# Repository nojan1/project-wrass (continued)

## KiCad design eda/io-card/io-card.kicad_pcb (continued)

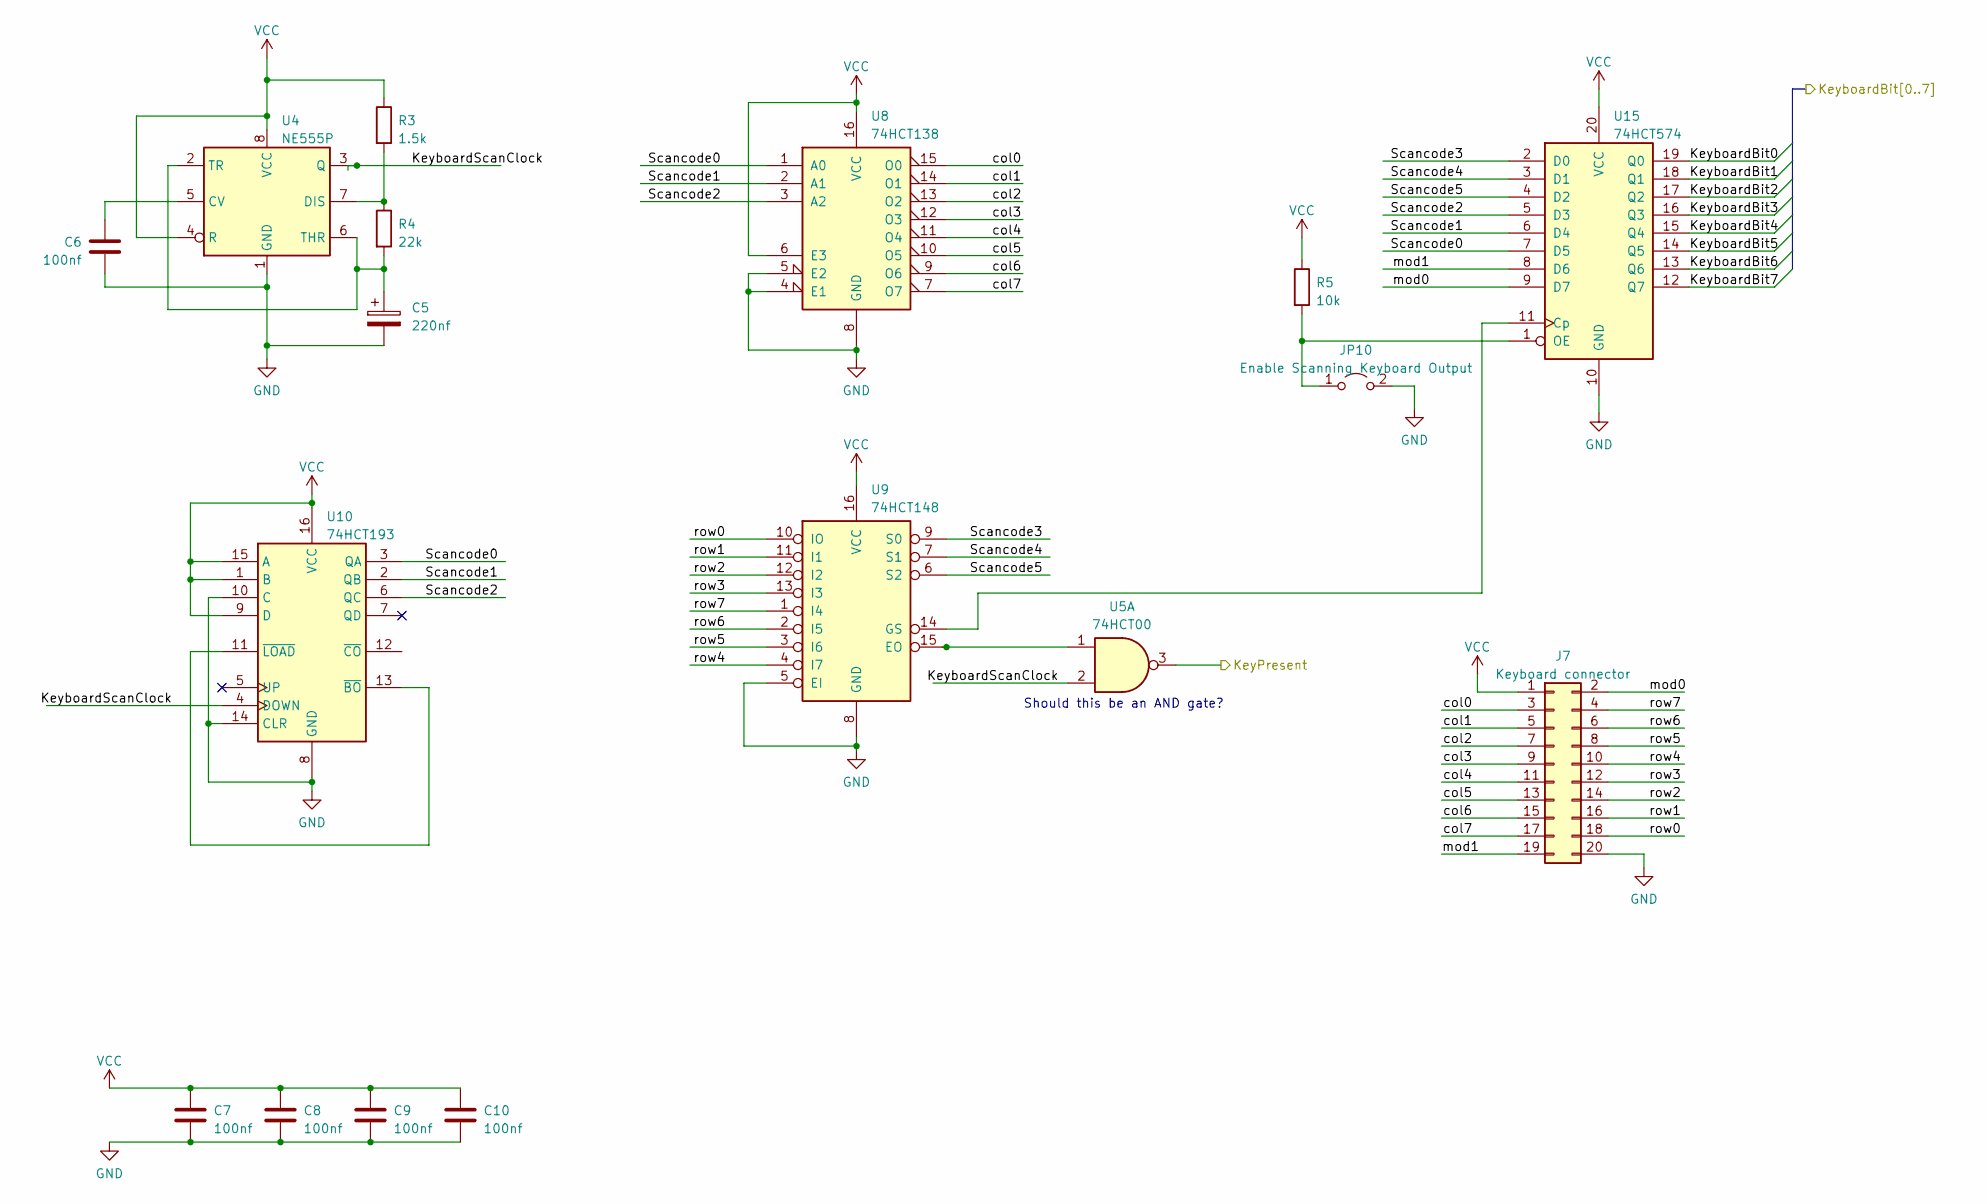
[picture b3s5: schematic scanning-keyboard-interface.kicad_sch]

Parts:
C5: 220nf; C_Radial_D4.0mm_H5.0mm_P1.50mm
C6, C7, C8, C9, C10: 100nf; C_Disc_D3.8mm_W2.6mm_P2.50mm
J7: Keyboard connector; PinHeader_2x10_P2.54mm_Horizontal
JP10: Enable Scanning Keyboard Output; PinHeader_1x02_P2.54mm_Vertical
R3: 1.5k; R_Axial_DIN0204_L3.6mm_D1.6mm_P5.08mm_Horizontal
R4: 22k; R_Axial_DIN0204_L3.6mm_D1.6mm_P5.08mm_Horizontal
R5: 10k; R_Axial_DIN0204_L3.6mm_D1.6mm_P5.08mm_Horizontal
U4: NE555P; DIP-8_W7.62mm
U5: 74HCT00; DIP-14_W7.62mm
U8: 74HCT138; DIP-16_W7.62mm
U9: 74HCT148; DIP-16_W7.62mm
U10: 74HCT193; DIP-16_W7.62mm
U15: 74HCT574; DIP-20_W7.62mm

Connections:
/PS2 keyboard interface/KeyboardBit0: U15.19 (Q0); also elsewhere on the board
/PS2 keyboard interface/KeyboardBit1: U15.18 (Q1); also elsewhere on the board
/PS2 keyboard interface/KeyboardBit2: U15.17 (Q2); also elsewhere on the board
/PS2 keyboard interface/KeyboardBit3: U15.16 (Q3); also elsewhere on the board
/PS2 keyboard interface/KeyboardBit4: U15.15 (Q4); also elsewhere on the board
/PS2 keyboard interface/KeyboardBit5: U15.14 (Q5); also elsewhere on the board
/PS2 keyboard interface/KeyboardBit6: U15.13 (Q6); also elsewhere on the board
/PS2 keyboard interface/KeyboardBit7: U15.12 (Q7); also elsewhere on the board
/Scanning keyboard interface/KeyPresent: U5.3; also elsewhere on the board
/Scanning keyboard interface/KeyboardScanClock: U4.3 (Q), U5.2, U10.4 (DOWN)
/Scanning keyboard interface/Scancode0: U8.1 (A0), U10.3 (QA), U15.7 (D5)
/Scanning keyboard interface/Scancode1: U8.2 (A1), U10.2 (QB), U15.6 (D4)
/Scanning keyboard interface/Scancode2: U8.3 (A2), U10.6 (QC), U15.5 (D3)
/Scanning keyboard interface/Scancode3: U9.9 (S0), U15.2 (D0)
/Scanning keyboard interface/Scancode4: U9.7 (S1), U15.3 (D1)
/Scanning keyboard interface/Scancode5: U9.6 (S2), U15.4 (D2)
/Scanning keyboard interface/col0: J7.3, U8.15 (O0)
/Scanning keyboard interface/col1: J7.5, U8.14 (O1)
/Scanning keyboard interface/col2: J7.7, U8.13 (O2)
/Scanning keyboard interface/col3: J7.9, U8.12 (O3)
/Scanning keyboard interface/col4: J7.11, U8.11 (O4)
/Scanning keyboard interface/col5: J7.13, U8.10 (O5)
/Scanning keyboard interface/col6: J7.15, U8.9 (O6)
/Scanning keyboard interface/col7: J7.17, U8.7 (O7)
/Scanning keyboard interface/mod0: J7.2, U15.9 (D7)
/Scanning keyboard interface/mod1: J7.19, U15.8 (D6)
/Scanning keyboard interface/row0: J7.18, U9.10 (IO)
/Scanning keyboard interface/row1: J7.16, U9.11 (I1)
/Scanning keyboard interface/row2: J7.14, U9.12 (I2)
/Scanning keyboard interface/row3: J7.12, U9.13 (I3)
/Scanning keyboard interface/row4: J7.10, U9.4 (I7)
/Scanning keyboard interface/row5: J7.8, U9.3 (I6)
/Scanning keyboard interface/row6: J7.6, U9.2 (I5)
/Scanning keyboard interface/row7: J7.4, U9.1 (I4)
GND: C5.2, C6.2, C7.2, C8.2, C9.2, C10.2, J7.20, JP10.2 (B), U4.1 (GND), U8.4 (E1), U8.5 (E2), U8.8 (GND), U9.5 (EI), U9.8 (GND), U10.8 (GND), U10.10 (C), U10.14 (CLR), U15.10 (GND); also elsewhere on the board
unnamed: JP10.1 (A), R5.2, U15.1 (OE)
unnamed: C6.1, U4.5 (CV)
unnamed: R3.2, R4.1, U4.7 (DIS)
unnamed: C5.1, R4.2, U4.2 (TR), U4.6 (THR)
unnamed: U5.1, U9.15 (EO)
unnamed: U10.11 (~LOAD), U10.13 (~BO)
unnamed: U9.14 (GS), U15.11 (Cp)
VCC: C7.1, C8.1, C9.1, C10.1, J7.1, R3.1, R5.1, U4.4 (R), U4.8 (VCC), U8.6 (E3), U8.16 (VCC), U9.16 (VCC), U10.1 (B), U10.9 (D), U10.15 (A), U10.16 (VCC), U15.20 (VCC); also elsewhere on the board

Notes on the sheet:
Should this be an AND gate?

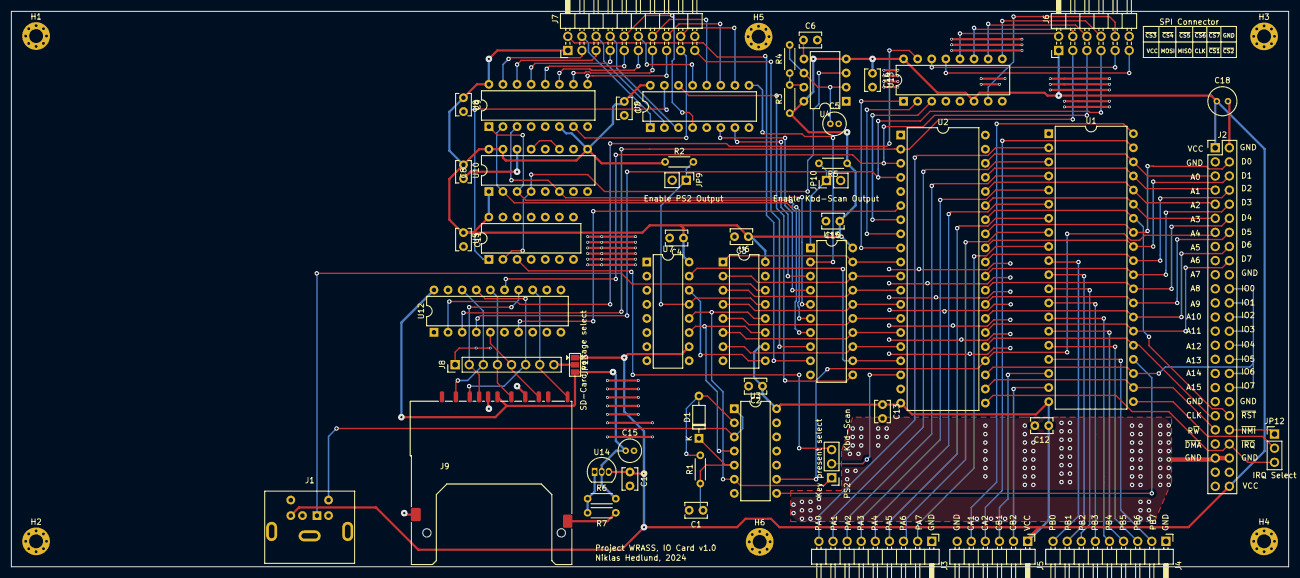
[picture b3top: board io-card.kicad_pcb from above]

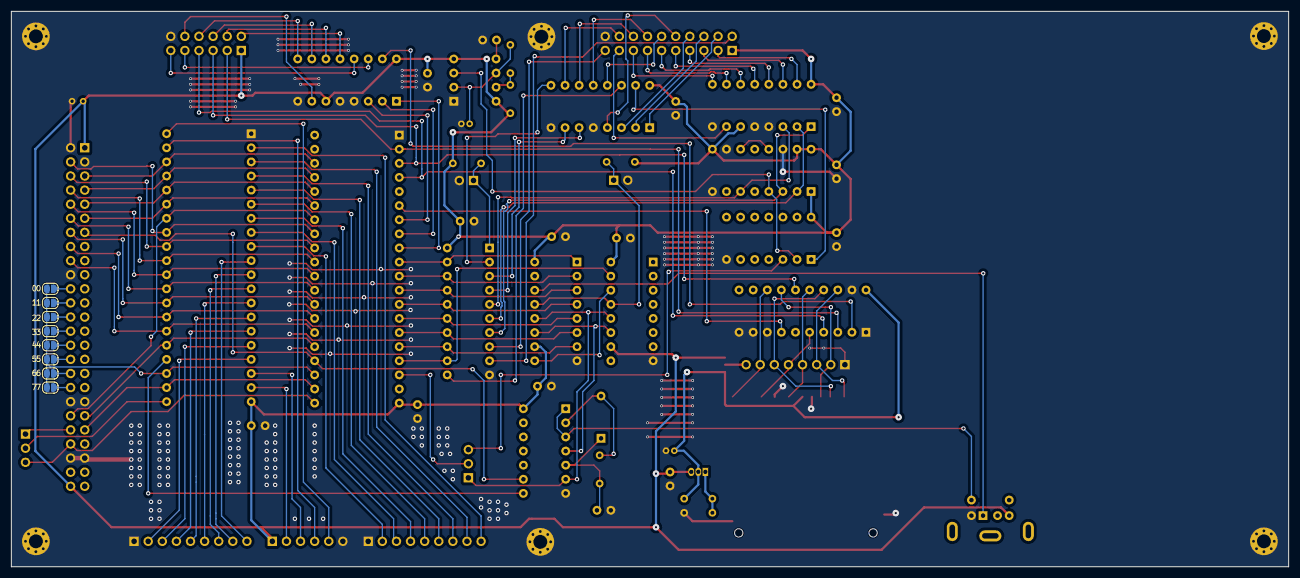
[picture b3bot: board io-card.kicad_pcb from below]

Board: 2 copper layers, 230.0 x 100.0 mm, 67 parts (8 on the bottom side), 125 nets.

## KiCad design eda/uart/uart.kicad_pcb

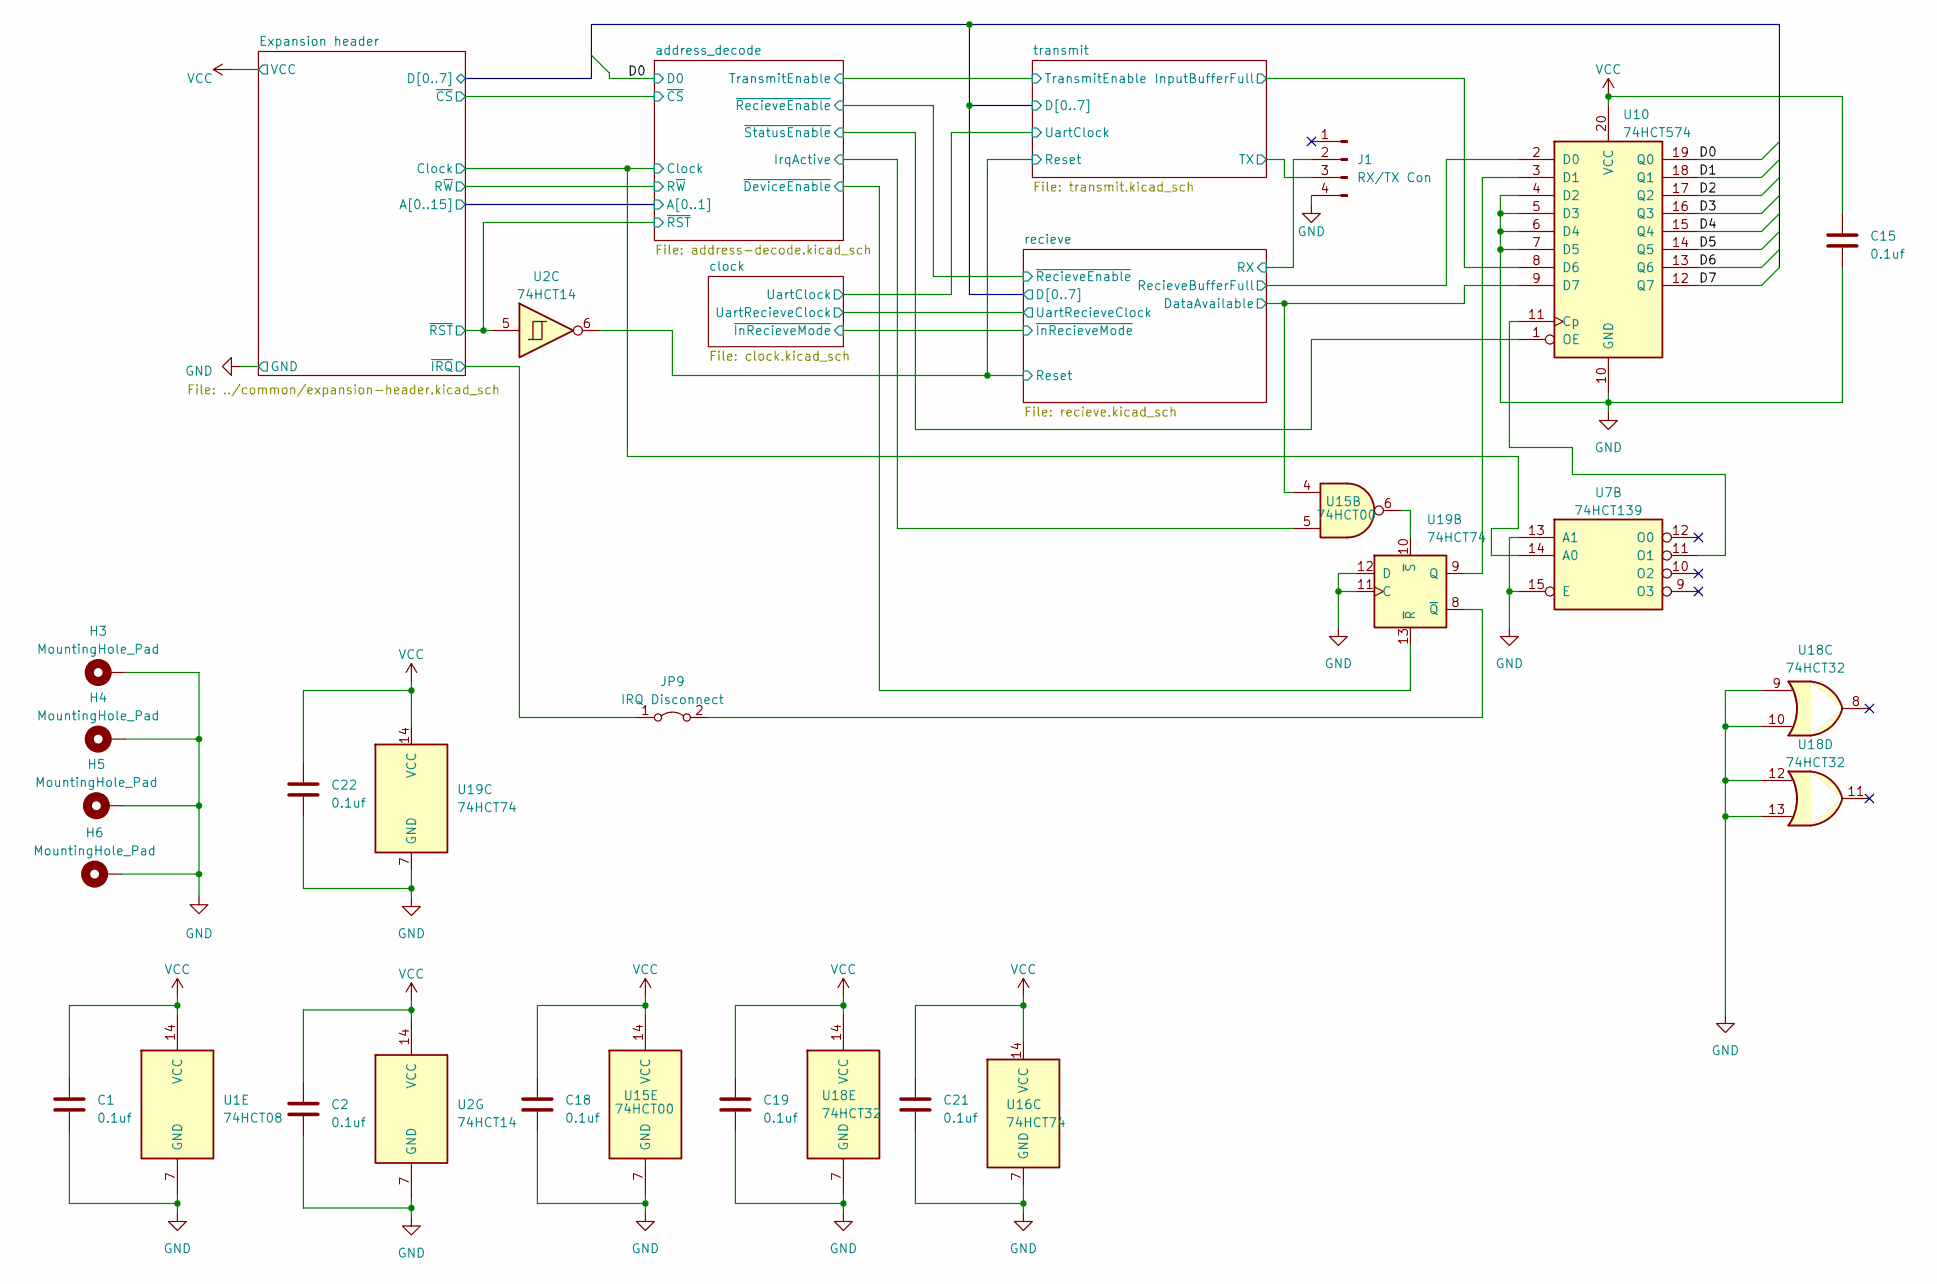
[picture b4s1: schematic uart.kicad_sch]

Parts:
C1, C2, C15, C18, C19, C21, C22: 0.1uf; C_Disc_D3.8mm_W2.6mm_P2.50mm
H3, H4, H5, H6: MountingHole_Pad; MountingHole_2.5mm_Pad_Via
J1: RX/TX Con; PinHeader_1x04_P2.54mm_Horizontal
JP9: IRQ Disconnect; PinHeader_1x02_P2.54mm_Vertical
U1: 74HCT08; DIP-14_W7.62mm
U2: 74HCT14; DIP-14_W7.62mm
U7: 74HCT139; DIP-16_W7.62mm
U10: 74HCT574; DIP-20_W7.62mm
U15: 74HCT00; DIP-14_W7.62mm
U16: 74HCT74; DIP-14_W10.16mm
U18: 74HCT32; DIP-14_W7.62mm
U19: 74HCT74; DIP-14_W7.62mm

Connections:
/Expansion header/Clock: U7.14 (A0); also elsewhere on the board
/Expansion header/D0: U10.19 (Q0); also elsewhere on the board
/Expansion header/D1: U10.18 (Q1); also elsewhere on the board
/Expansion header/D2: U10.17 (Q2); also elsewhere on the board
/Expansion header/D3: U10.16 (Q3); also elsewhere on the board
/Expansion header/D4: U10.15 (Q4); also elsewhere on the board
/Expansion header/D5: U10.14 (Q5); also elsewhere on the board
/Expansion header/D6: U10.13 (Q6); also elsewhere on the board
/Expansion header/D7: U10.12 (Q7); also elsewhere on the board
/Expansion header/~IRQ: JP9.1 (A); also elsewhere on the board
/Expansion header/~RST: U2.5; also elsewhere on the board
/address_decode/IrqActive: U15.5; also elsewhere on the board
/address_decode/~DeviceEnable: U19.13 (~R); also elsewhere on the board
/address_decode/~StatusEnable: U10.1 (OE); also elsewhere on the board
/recieve/DataAvailable: U1.11, U10.9 (D7), U15.4
/recieve/RX: J1.2; also elsewhere on the board
/recieve/RecieveBufferFull: U1.8, U10.2 (D0)
/recieve/Reset: U2.6; also elsewhere on the board
/transmit/InputBufferFull: U10.8 (D6); also elsewhere on the board
/transmit/TX: J1.3; also elsewhere on the board
GND: C1.2, C2.2, C15.2, C18.2, C19.2, C21.2, C22.2, H3.1, H4.1, H5.1, H6.1, J1.4, U1.7 (GND), U2.7 (GND), U7.13 (A1), U7.15 (E), U10.4 (D2), U10.5 (D3), U10.6 (D4), U10.7 (D5), U10.10 (GND), U15.7 (GND), U16.7 (GND), U18.7 (GND), U18.9, U18.10, U18.12, U18.13, U19.7 (GND), U19.11 (C), U19.12 (D); also elsewhere on the board
unnamed: JP9.2 (B), U19.8 (~Q)
unnamed: U7.11 (O1), U10.11 (Cp)
unnamed: U10.3 (D1), U19.9 (Q)
unnamed 91: U1.10; also elsewhere on the board
unnamed 92: U1.12; also elsewhere on the board
unnamed 93: U1.9; also elsewhere on the board
unnamed 94: U1.13; also elsewhere on the board
unnamed: U15.6, U19.10 (~S)
VCC: C1.1, C2.1, C15.1, C18.1, C19.1, C21.1, C22.1, U1.14 (VCC), U2.14 (VCC), U10.20 (VCC), U15.14 (VCC), U16.14 (VCC), U18.14 (VCC), U19.14 (VCC); also elsewhere on the board

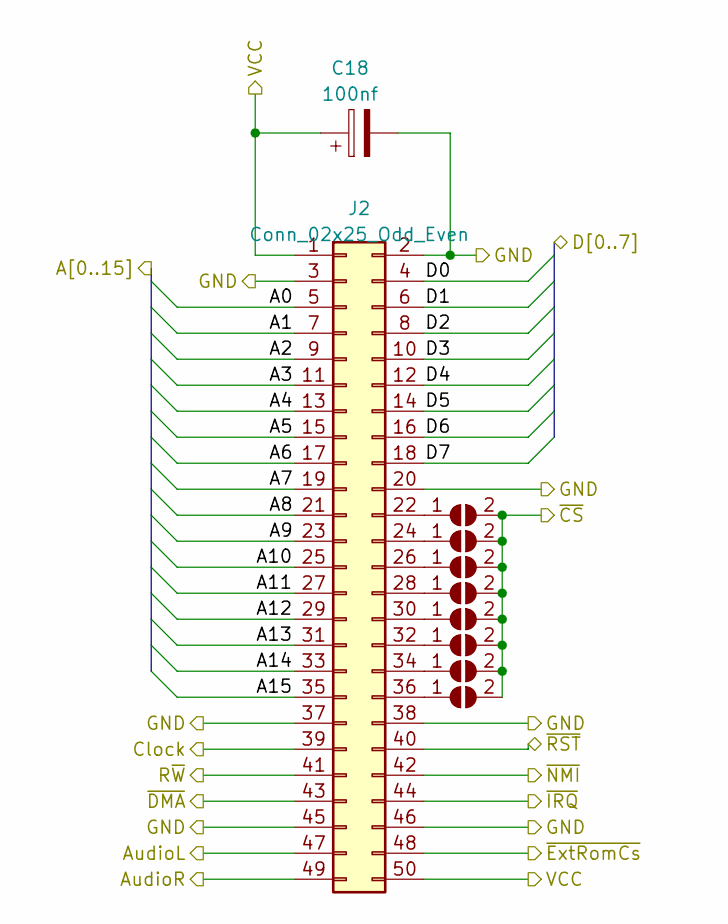
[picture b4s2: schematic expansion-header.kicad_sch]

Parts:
C18: 100nf; C_Radial_D5.0mm_H7.0mm_P2.00mm
J2: Conn_02x25_Odd_Even; PinHeader_2x25_P2.54mm_Vertical
JP1, JP2, JP3, JP4, JP5, JP6, JP7, JP8: SolderJumper_2_Open; SolderJumper-2_P1.3mm_Open_RoundedPad1.0x1.5mm

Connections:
/Expansion header/A0: J2.5; also elsewhere on the board
/Expansion header/A1: J2.7; also elsewhere on the board
/Expansion header/A2: J2.9
/Expansion header/A3: J2.11
/Expansion header/A4: J2.13
/Expansion header/A5: J2.15
/Expansion header/A6: J2.17
/Expansion header/A7: J2.19
/Expansion header/A8: J2.21
/Expansion header/A9: J2.23
/Expansion header/A10: J2.25
/Expansion header/A11: J2.27
/Expansion header/A12: J2.29
/Expansion header/A13: J2.31
/Expansion header/A14: J2.33
/Expansion header/A15: J2.35
/Expansion header/AudioL: J2.47
/Expansion header/AudioR: J2.49
/Expansion header/Clock: J2.39; also elsewhere on the board
/Expansion header/D0: J2.4; also elsewhere on the board
/Expansion header/D1: J2.6; also elsewhere on the board
/Expansion header/D2: J2.8; also elsewhere on the board
/Expansion header/D3: J2.10; also elsewhere on the board
/Expansion header/D4: J2.12; also elsewhere on the board
/Expansion header/D5: J2.14; also elsewhere on the board
/Expansion header/D6: J2.16; also elsewhere on the board
/Expansion header/D7: J2.18; also elsewhere on the board
/Expansion header/R~W: J2.41; also elsewhere on the board
/Expansion header/~CS: JP1.2 (B), JP2.2 (B), JP3.2 (B), JP4.2 (B), JP5.2 (B), JP6.2 (B), JP7.2 (B), JP8.2 (B); also elsewhere on the board
/Expansion header/~DMA: J2.43
/Expansion header/~ExtRomCs: J2.48
/Expansion header/~IRQ: J2.44; also elsewhere on the board
/Expansion header/~NMI: J2.42
/Expansion header/~RST: J2.40; also elsewhere on the board
GND: C18.2, J2.2, J2.3, J2.20, J2.37, J2.38, J2.45, J2.46; also elsewhere on the board
unnamed: J2.22, JP1.1 (A)
unnamed: J2.24, JP2.1 (A)
unnamed: J2.26, JP3.1 (A)
unnamed: J2.28, JP4.1 (A)
unnamed: J2.30, JP5.1 (A)
unnamed: J2.32, JP6.1 (A)
unnamed: J2.34, JP7.1 (A)
unnamed: J2.36, JP8.1 (A)
VCC: C18.1, J2.1, J2.50; also elsewhere on the board

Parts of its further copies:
C3: 100nf; C_Radial_D5.0mm_H7.0mm_P2.00mm

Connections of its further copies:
GND: C3.2; also elsewhere on the board
VCC: C3.1; also elsewhere on the board

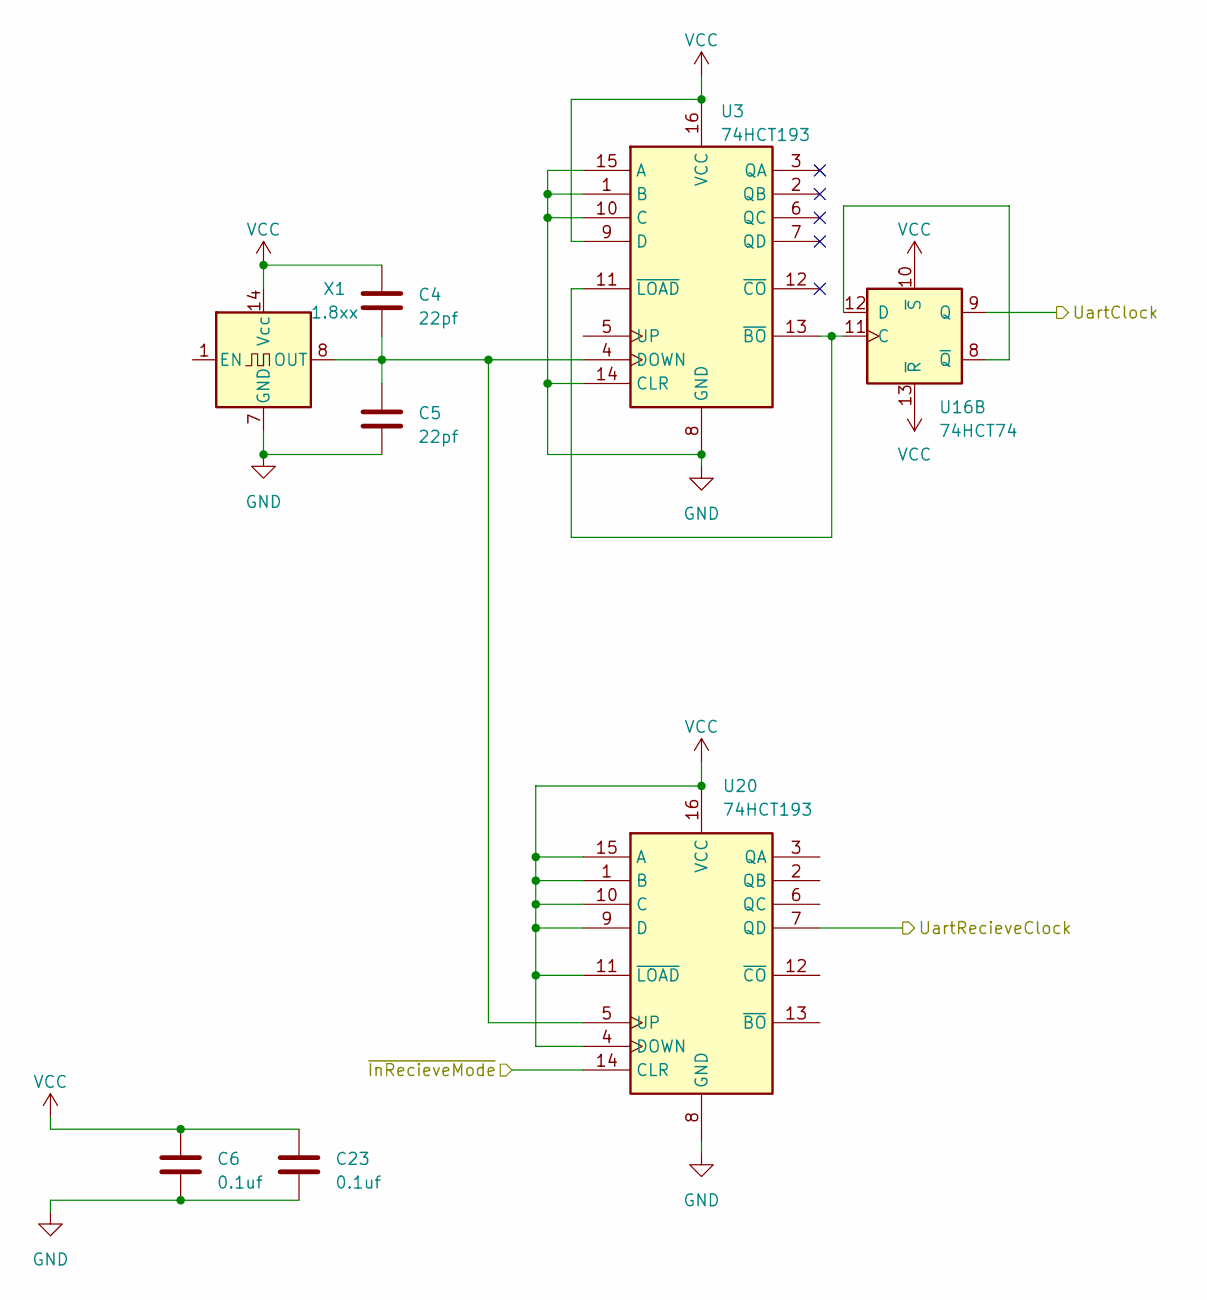
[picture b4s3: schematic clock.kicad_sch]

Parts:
C4, C5: 22pf; C_Disc_D3.8mm_W2.6mm_P2.50mm
C6, C23: 0.1uf; C_Disc_D3.8mm_W2.6mm_P2.50mm
U3, U20: 74HCT193; DIP-16_W7.62mm
U16: 74HCT74; DIP-14_W10.16mm
X1: 1.8xx; Oscillator_DIP-14

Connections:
/clock/UartClock: U16.9 (Q); also elsewhere on the board
/clock/UartRecieveClock: U20.7 (QD); also elsewhere on the board
/clock/~InRecieveMode: U20.14 (CLR); also elsewhere on the board
GND: C5.2, C6.2, C23.2, U3.1 (B), U3.8 (GND), U3.10 (C), U3.14 (CLR), U3.15 (A), U20.8 (GND), X1.7 (GND); also elsewhere on the board
unnamed: U3.11 (~LOAD), U3.13 (~BO), U16.11 (C)
unnamed: U16.8 (~Q), U16.12 (D)
unnamed: C4.2, C5.1, U3.4 (DOWN), U20.5 (UP), X1.8 (OUT)
VCC: C4.1, C6.1, C23.1, U3.9 (D), U3.16 (VCC), U16.10 (~S), U16.13 (~R), U20.1 (B), U20.4 (DOWN), U20.9 (D), U20.10 (C), U20.11 (~LOAD), U20.15 (A), U20.16 (VCC), X1.14 (Vcc); also elsewhere on the board

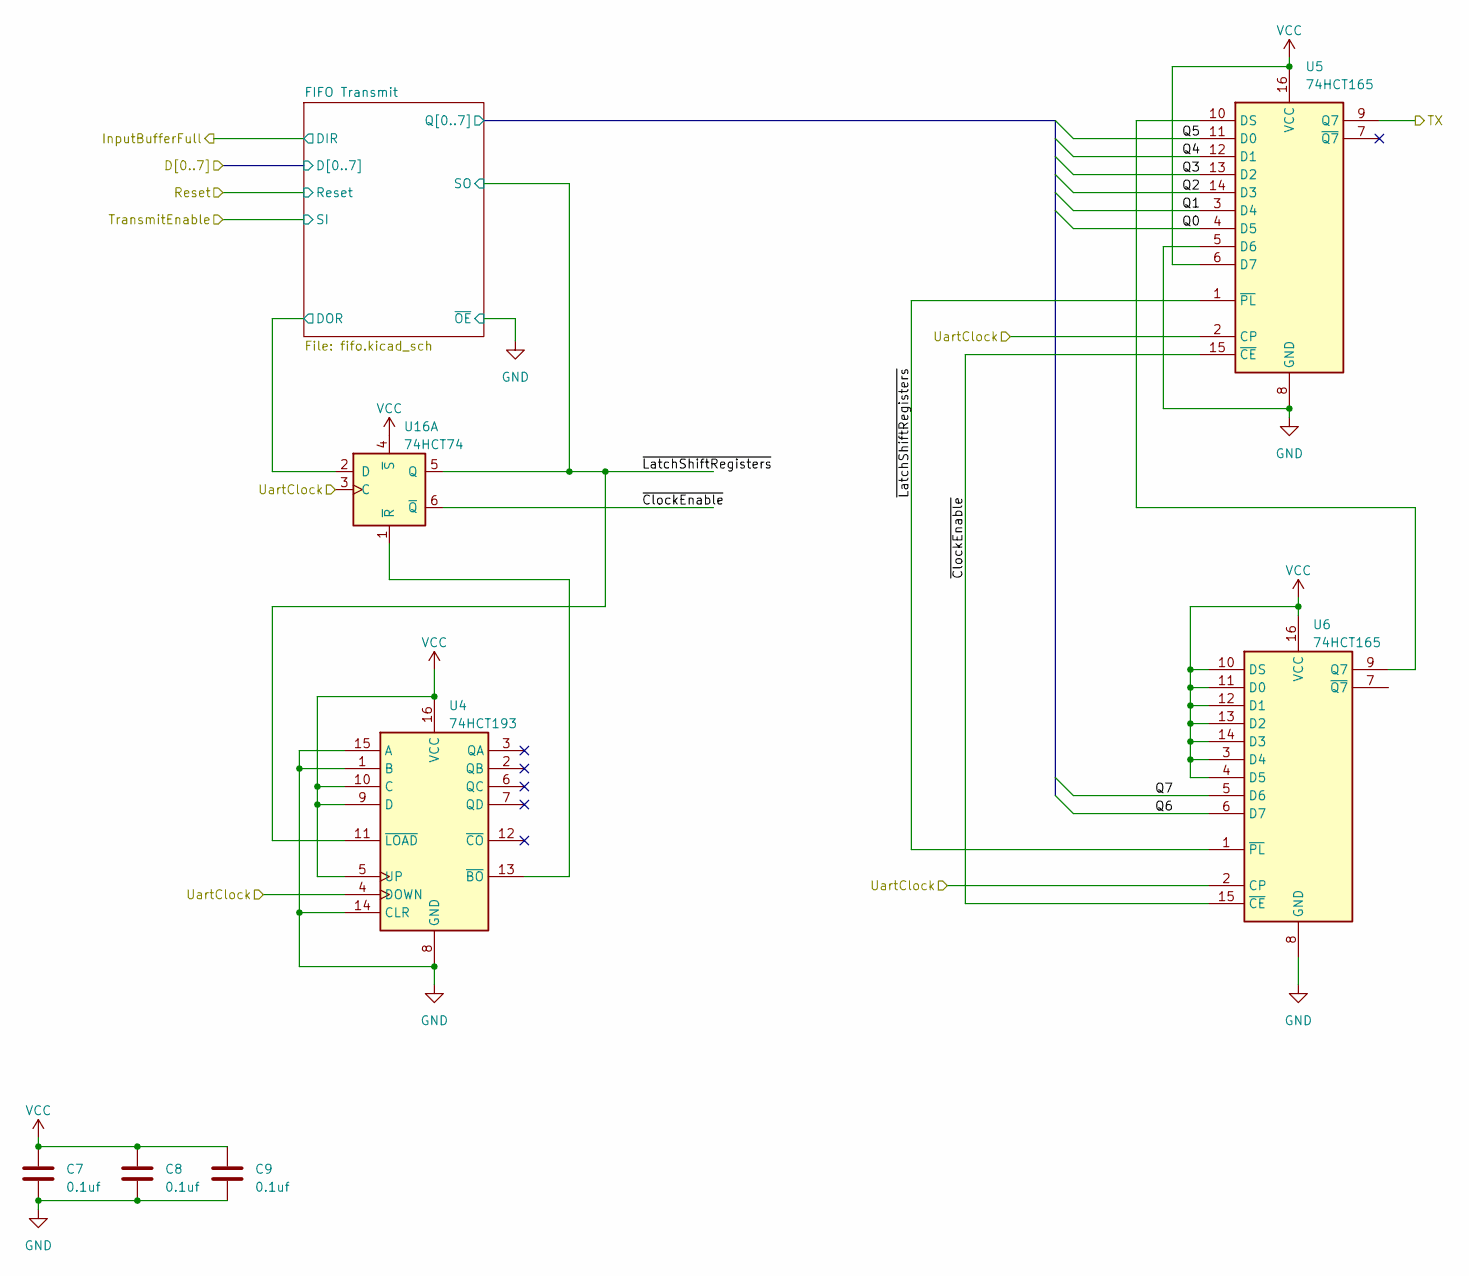
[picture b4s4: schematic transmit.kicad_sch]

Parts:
C7, C8, C9: 0.1uf; C_Disc_D3.8mm_W2.6mm_P2.50mm
U4: 74HCT193; DIP-16_W7.62mm
U5, U6: 74HCT165; DIP-16_W7.62mm
U16: 74HCT74; DIP-14_W10.16mm

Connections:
/clock/UartClock: U4.4 (DOWN), U5.2 (CP), U6.2 (CP), U16.3 (C); also elsewhere on the board
/transmit/FIFO Transmit/DOR: U16.2 (D); also elsewhere on the board
/transmit/FIFO Transmit/Q0: U5.4 (D5); also elsewhere on the board
/transmit/FIFO Transmit/Q1: U5.3 (D4); also elsewhere on the board
/transmit/FIFO Transmit/Q2: U5.14 (D3); also elsewhere on the board
/transmit/FIFO Transmit/Q3: U5.13 (D2); also elsewhere on the board
/transmit/FIFO Transmit/Q4: U5.12 (D1); also elsewhere on the board
/transmit/FIFO Transmit/Q5: U5.11 (D0); also elsewhere on the board
/transmit/FIFO Transmit/Q6: U6.6 (D7); also elsewhere on the board
/transmit/FIFO Transmit/Q7: U6.5 (D6); also elsewhere on the board
/transmit/TX: U5.9 (Q7); also elsewhere on the board
/transmit/~ClockEnable: U5.15 (~CE), U6.15 (~CE), U16.6 (~Q)
/transmit/~LatchShiftRegisters: U4.11 (~LOAD), U5.1 (~PL), U6.1 (~PL), U16.5 (Q); also elsewhere on the board
GND: C7.2, C8.2, C9.2, U4.1 (B), U4.8 (GND), U4.14 (CLR), U4.15 (A), U5.5 (D6), U5.8 (GND), U6.8 (GND); also elsewhere on the board
unnamed: U5.10 (DS), U6.9 (Q7)
unnamed: U4.13 (~BO), U16.1 (~R)
VCC: C7.1, C8.1, C9.1, U4.5 (UP), U4.9 (D), U4.10 (C), U4.16 (VCC), U5.6 (D7), U5.16 (VCC), U6.3 (D4), U6.4 (D5), U6.10 (DS), U6.11 (D0), U6.12 (D1), U6.13 (D2), U6.14 (D3), U6.16 (VCC), U16.4 (~S); also elsewhere on the board

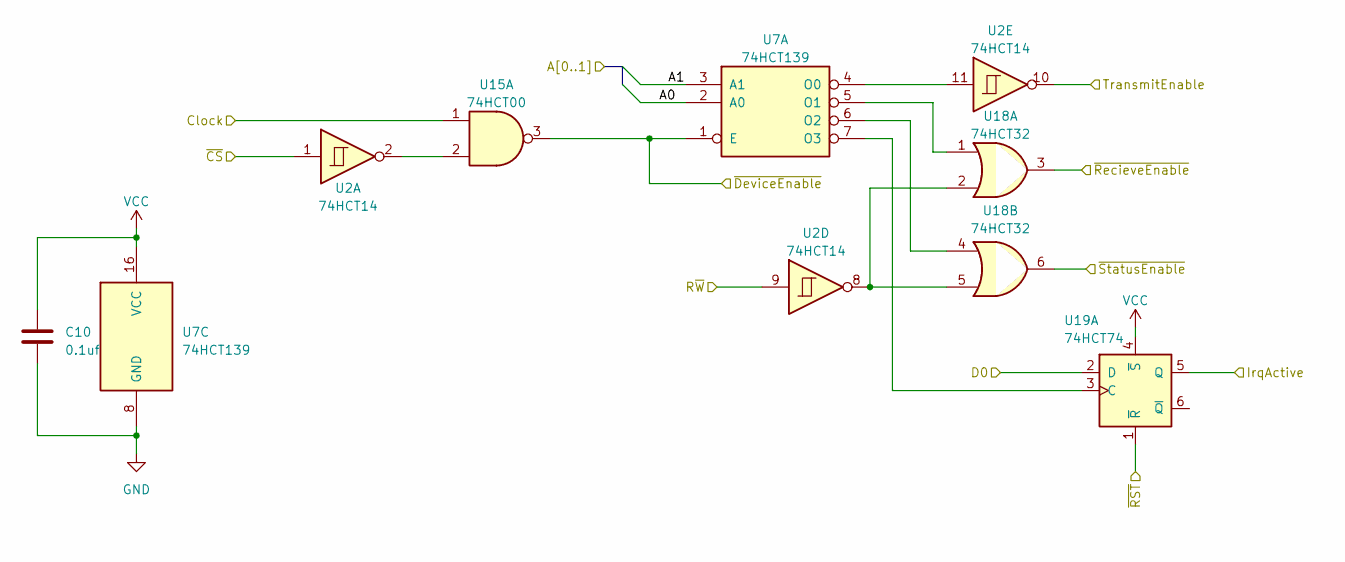
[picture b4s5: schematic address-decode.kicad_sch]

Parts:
C10: 0.1uf; C_Disc_D3.8mm_W2.6mm_P2.50mm
U2: 74HCT14; DIP-14_W7.62mm
U7: 74HCT139; DIP-16_W7.62mm
U15: 74HCT00; DIP-14_W7.62mm
U18: 74HCT32; DIP-14_W7.62mm
U19: 74HCT74; DIP-14_W7.62mm

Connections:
/Expansion header/A0: U7.2 (A0); also elsewhere on the board
/Expansion header/A1: U7.3 (A1); also elsewhere on the board
/Expansion header/Clock: U15.1; also elsewhere on the board
/Expansion header/D0: U19.2 (D); also elsewhere on the board
/Expansion header/R~W: U2.9; also elsewhere on the board
/Expansion header/~CS: U2.1; also elsewhere on the board
/Expansion header/~RST: U19.1 (~R); also elsewhere on the board
/address_decode/IrqActive: U19.5 (Q); also elsewhere on the board
/address_decode/TransmitEnable: U2.10; also elsewhere on the board
/address_decode/~DeviceEnable: U7.1 (E), U15.3; also elsewhere on the board
/address_decode/~RecieveEnable: U18.3; also elsewhere on the board
/address_decode/~StatusEnable: U18.6; also elsewhere on the board
GND: C10.2, U7.8 (GND); also elsewhere on the board
unnamed: U2.11, U7.4 (O0)
unnamed: U7.5 (O1), U18.1
unnamed: U7.6 (O2), U18.4
unnamed: U2.2, U15.2
unnamed: U2.8, U18.2, U18.5
unnamed: U7.7 (O3), U19.3 (C)
VCC: C10.1, U7.16 (VCC), U19.4 (~S); also elsewhere on the board

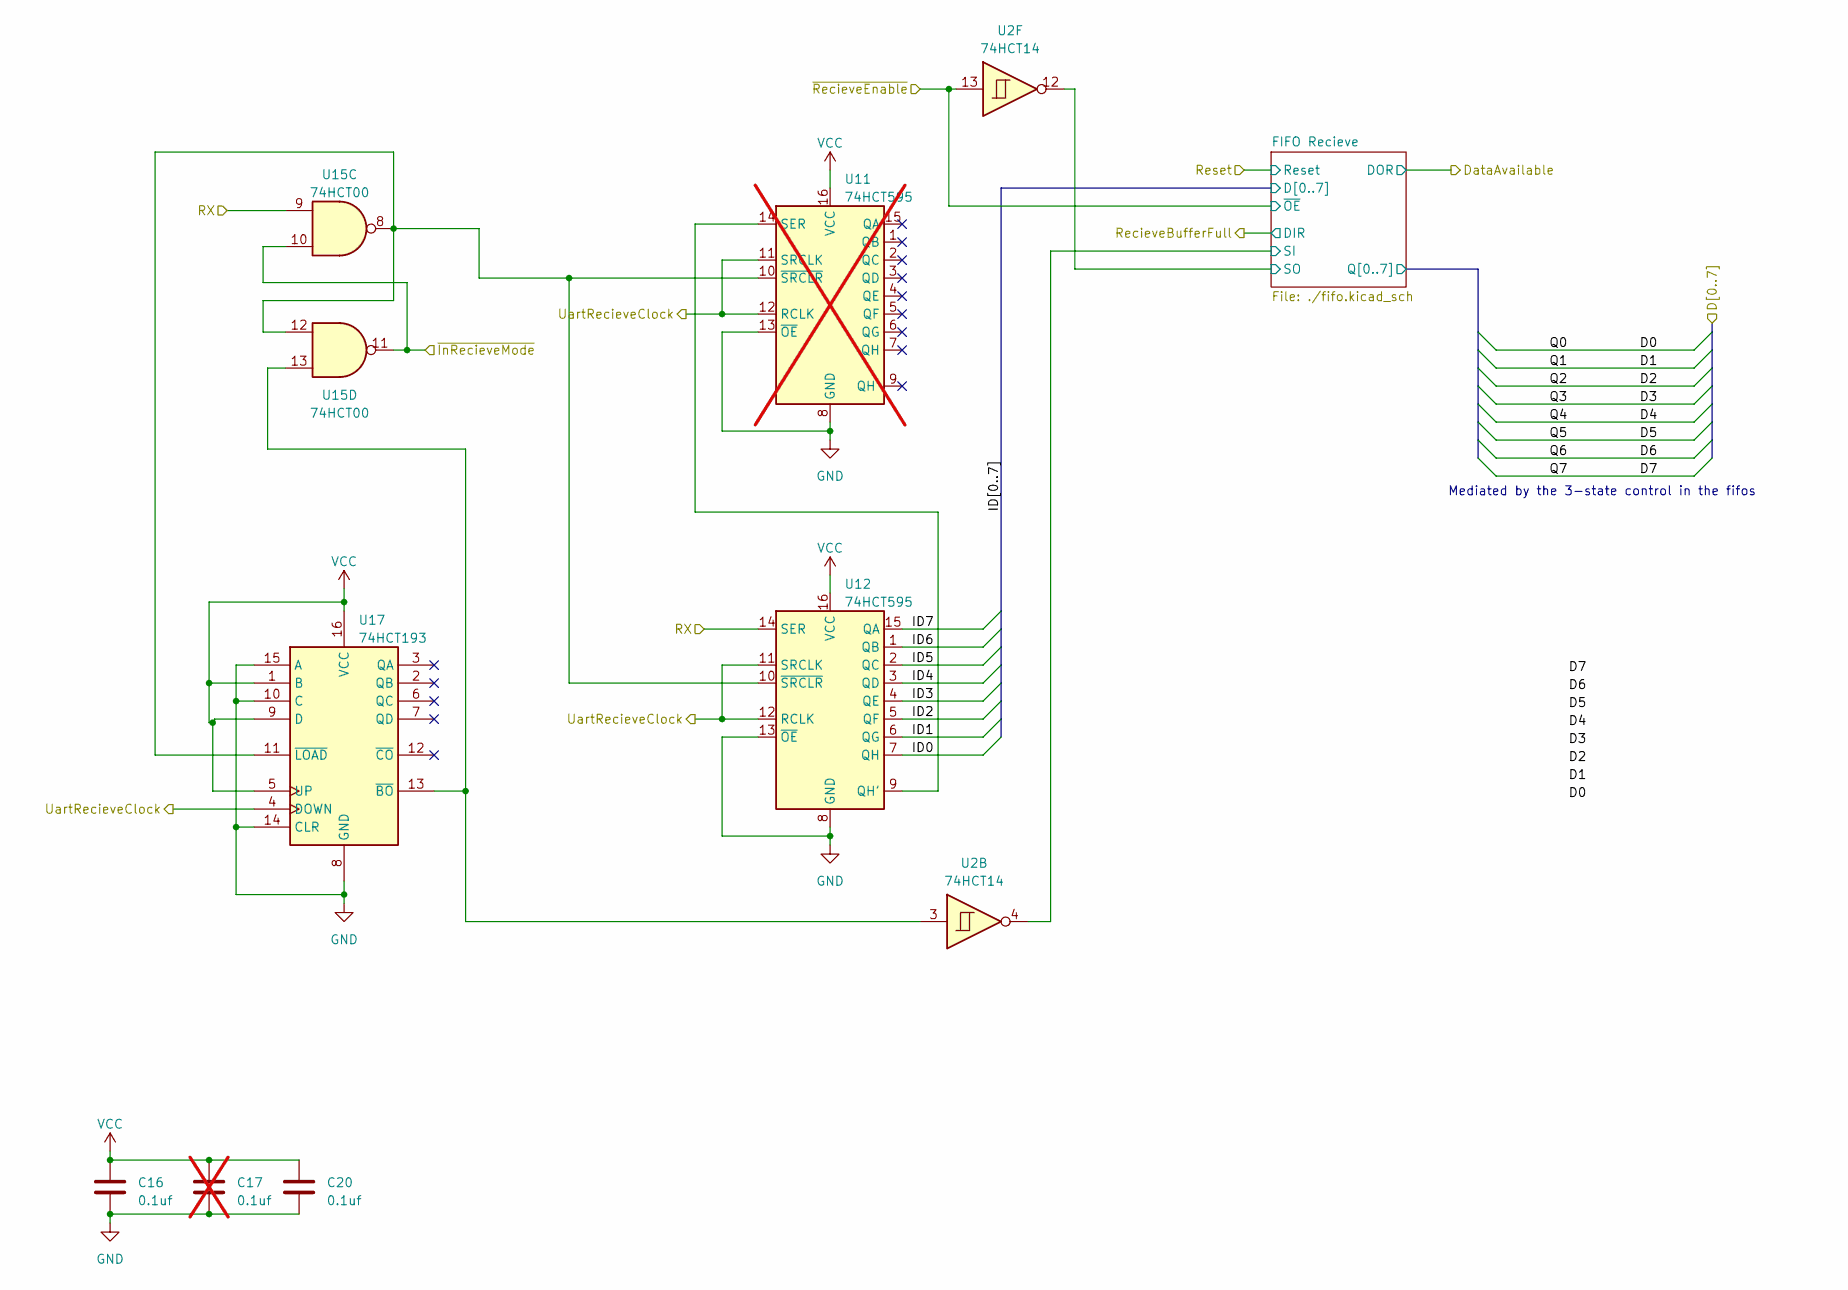
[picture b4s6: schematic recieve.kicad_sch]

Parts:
C16, C20: 0.1uf; C_Disc_D3.8mm_W2.6mm_P2.50mm
C17: 0.1uf; C_Disc_D3.8mm_W2.6mm_P2.50mm; not fitted
U2: 74HCT14; DIP-14_W7.62mm
U11: 74HCT595; DIP-16_W7.62mm; not fitted
U12: 74HCT595; DIP-16_W7.62mm
U15: 74HCT00; DIP-14_W7.62mm
U17: 74HCT193; DIP-16_W7.62mm

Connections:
/address_decode/~RecieveEnable: U2.13; also elsewhere on the board
/clock/UartRecieveClock: U11.11 (SRCLK), U11.12 (RCLK), U12.11 (SRCLK), U12.12 (RCLK), U17.4 (DOWN); also elsewhere on the board
/clock/~InRecieveMode: U15.10, U15.11; also elsewhere on the board
/recieve/FIFO Recieve/SI: U2.4; also elsewhere on the board
/recieve/FIFO Recieve/SO: U2.12; also elsewhere on the board
/recieve/ID0: U12.7 (QH); also elsewhere on the board
/recieve/ID1: U12.6 (QG); also elsewhere on the board
/recieve/ID2: U12.5 (QF); also elsewhere on the board
/recieve/ID3: U12.4 (QE); also elsewhere on the board
/recieve/ID4: U12.3 (QD); also elsewhere on the board
/recieve/ID5: U12.2 (QC); also elsewhere on the board
/recieve/ID6: U12.1 (QB); also elsewhere on the board
/recieve/ID7: U12.15 (QA); also elsewhere on the board
/recieve/RX: U12.14 (SER), U15.9; also elsewhere on the board
GND: C16.2, C17.2, C20.2, U11.8 (GND), U11.13 (~OE), U12.8 (GND), U12.13 (~OE), U17.8 (GND), U17.10 (C), U17.14 (CLR), U17.15 (A); also elsewhere on the board
unnamed: U11.14 (SER), U12.9 (QH')
unnamed: U11.10 (~SRCLR), U12.10 (~SRCLR), U15.8, U15.12, U17.11 (~LOAD)
unnamed: U2.3, U15.13, U17.13 (~BO)
VCC: C16.1, C17.1, C20.1, U11.16 (VCC), U12.16 (VCC), U17.1 (B), U17.5 (UP), U17.9 (D), U17.16 (VCC); also elsewhere on the board

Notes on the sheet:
Mediated by the 3-state control in the fifos
